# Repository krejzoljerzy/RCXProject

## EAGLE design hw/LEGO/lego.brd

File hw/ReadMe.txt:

Tutaj wrzucamy wszystkie smieci odnosnie hardware'u ;)

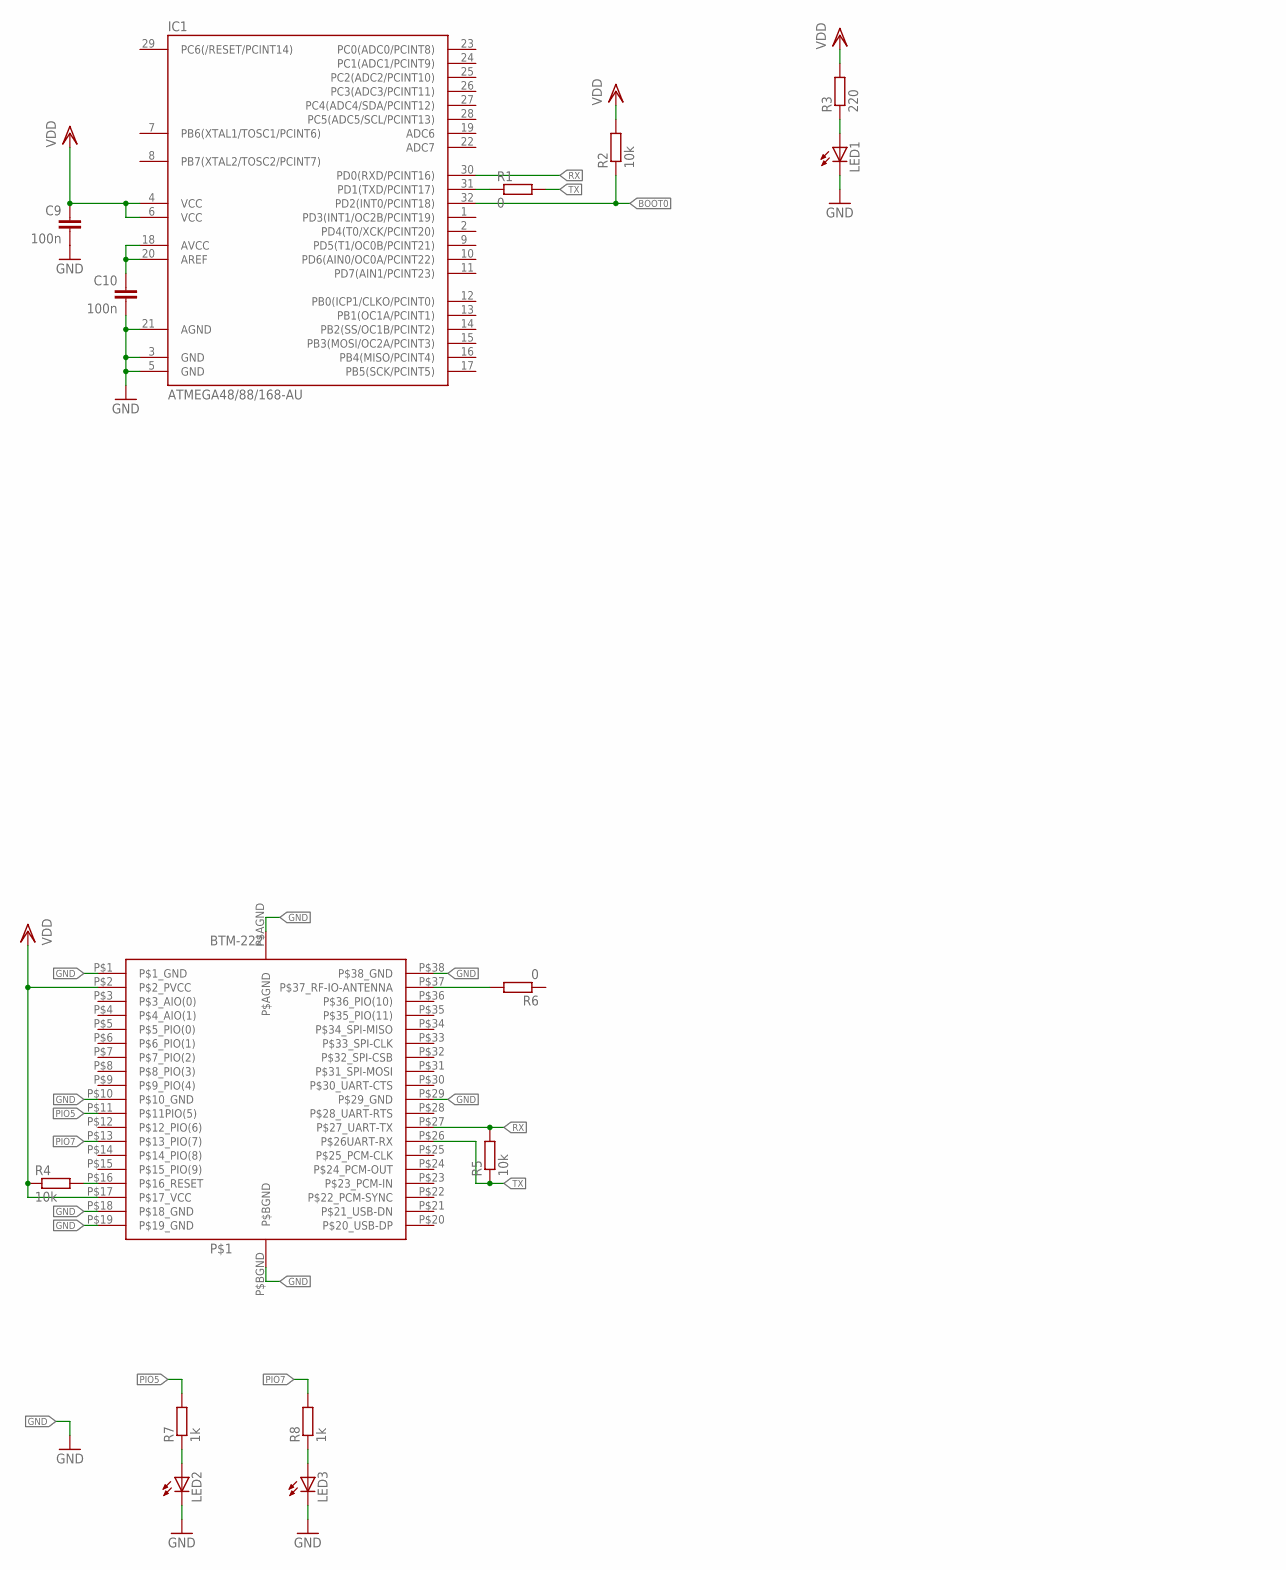
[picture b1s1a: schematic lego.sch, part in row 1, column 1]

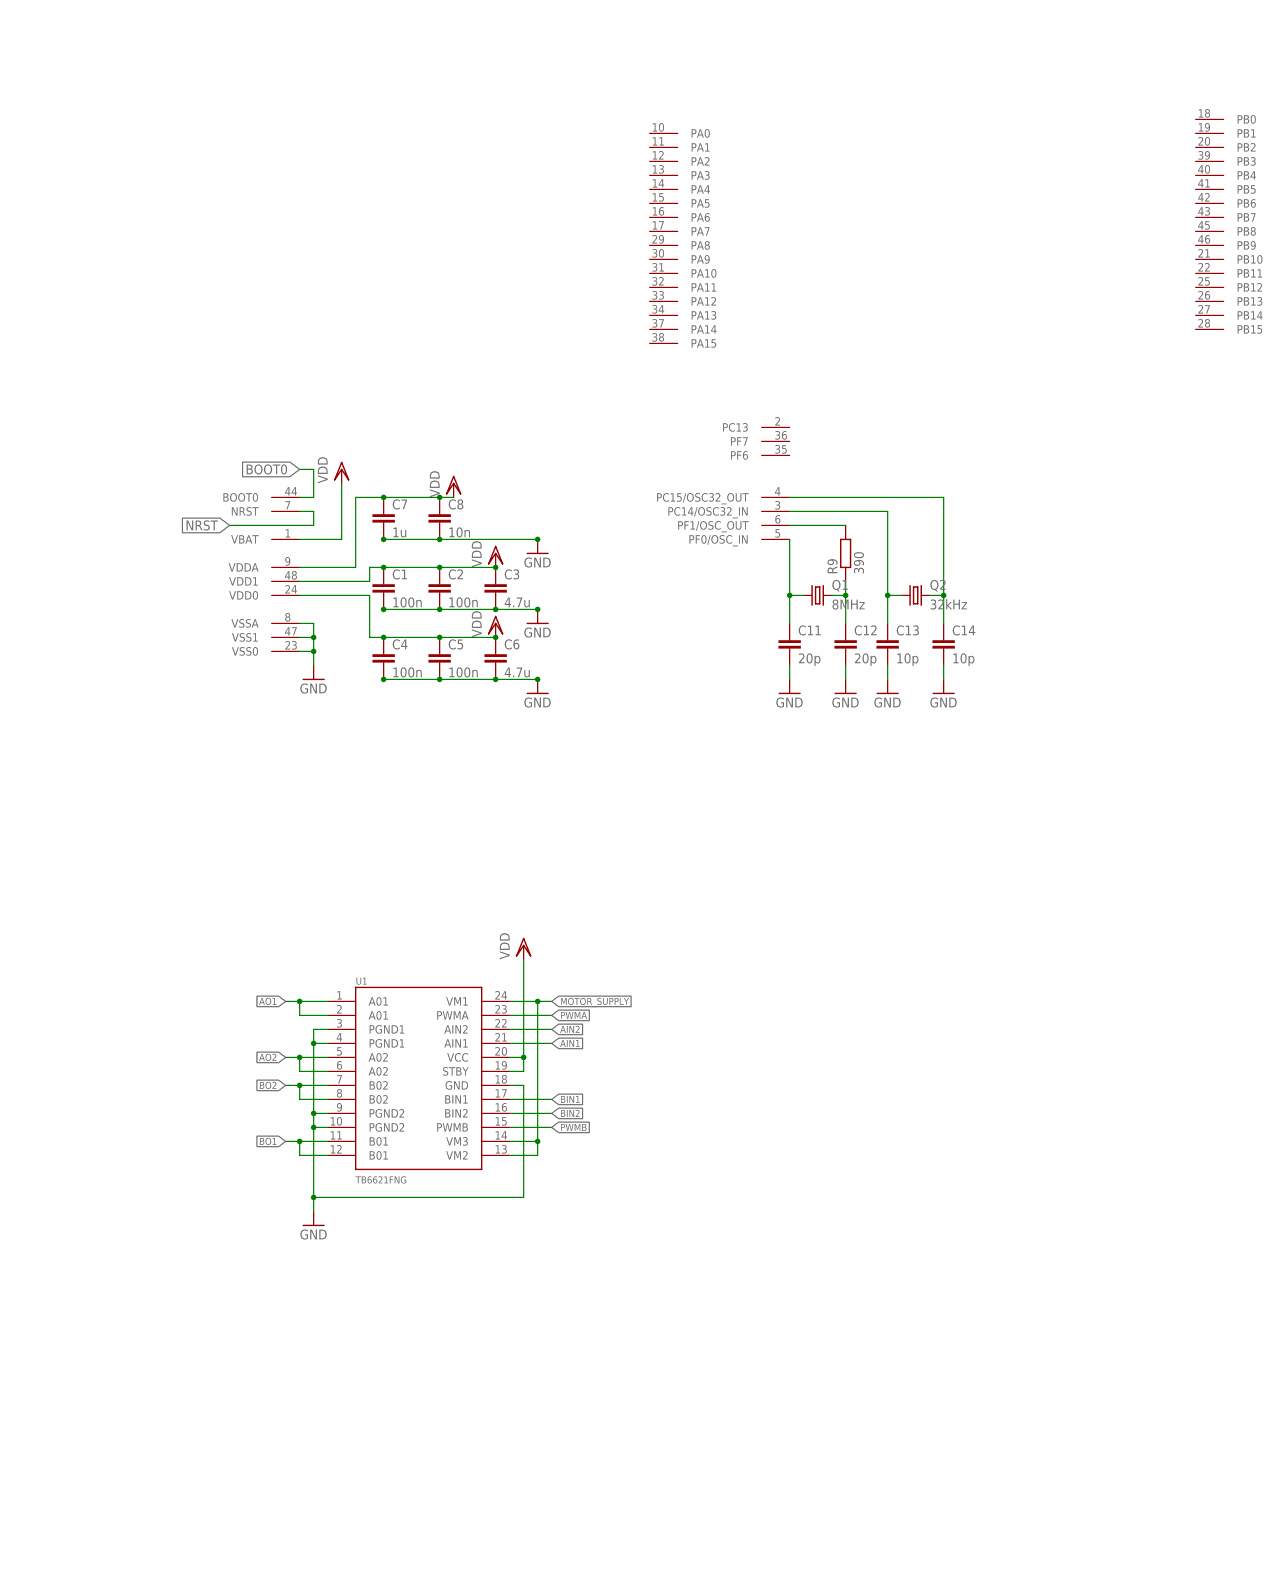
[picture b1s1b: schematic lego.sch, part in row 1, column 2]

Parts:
C1, C2, C4, C5, C9, C10: 100n; C0805
C3, C6: 4.7u; C0805
C7: 1u; C0805
C8: 10n; C0805
C11, C12: 20p; C0805
C13, C14: 10p; C0805
IC1: ATMEGA48/88/168-AU; TQFP32-08
LED1, LED2, LED3: LEDSMT1206; 1206
P$1: BTM-222
Q1: 8MHz; HC49UP
Q2: 32kHz; HC49UP
R1, R6: 0; R0805
R2, R4, R5: 10k; R0805
R3: 220; R0805
R7, R8: 1k; R0805
R9: 390; R0805
U1: TB6621FNG; SSOP24
U$1: STM32F050; LQFP48

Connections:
AIN1: U1.21 (AIN1)
AIN2: U1.22 (AIN2)
AO1: U1.1 (A01), U1.2 (A01)
AO2: U1.5 (A02), U1.6 (A02)
BIN1: U1.17 (BIN1)
BIN2: U1.16 (BIN2)
BO1: U1.11 (B01), U1.12 (B01)
BO2: U1.7 (B02), U1.8 (B02)
BOOT0: IC1.32 (PD2(INT0/PCINT18)), R2.1, U$1.44 (BOOT0)
GND: C1.2, C2.2, C3.2, C4.2, C5.2, C6.2, C7.2, C8.2, C9.2, C10.2, C11.2, C12.2, C13.2, C14.2, IC1.3 (GND), IC1.5 (GND), IC1.21 (AGND), LED1.C, LED2.C, LED3.C, P$1.P$1 (P$1_GND), P$1.P$10 (P$10_GND), P$1.P$18 (P$18_GND), P$1.P$19 (P$19_GND), P$1.P$29 (P$29_GND), P$1.P$38 (P$38_GND), P$1.P$AGND, P$1.P$BGND, U1.3 (PGND1), U1.4 (PGND1), U1.9 (PGND2), U1.10 (PGND2), U1.18 (GND), U$1.8 (VSSA), U$1.23 (VSS0), U$1.47 (VSS1)
MOTOR_SUPPLY: U1.13 (VM2), U1.14 (VM3), U1.24 (VM1)
unnamed: IC1.31 (PD1(TXD/PCINT17)), R1.1
unnamed: C10.1, IC1.18 (AVCC), IC1.20 (AREF)
unnamed: LED1.A, R3.1
unnamed: P$1.P$16 (P$16_RESET), R4.2
unnamed: P$1.P$37 (P$37_RF-IO-ANTENNA), R6.2
unnamed: LED2.A, R7.1
unnamed: LED3.A, R8.1
unnamed: R9.2, U$1.6 (PF1/OSC_OUT)
unnamed: C11.1, Q1.1, U$1.5 (PF0/OSC_IN)
unnamed: C12.1, Q1.2, R9.1
unnamed: C13.1, Q2.1, U$1.3 (PC14/OSC32_IN)
unnamed: C14.1, Q2.2, U$1.4 (PC15/OSC32_OUT)
NRST: U$1.7 (NRST)
PIO5: P$1.P$11 (P$11PIO(5)), R7.2
PIO7: P$1.P$13 (P$13_PIO(7)), R8.2
PWMA: U1.23 (PWMA)
PWMB: U1.15 (PWMB)
RX: IC1.30 (PD0(RXD/PCINT16)), P$1.P$27 (P$27_UART-TX), R5.2
TX: P$1.P$26 (P$26UART-RX), R1.2, R5.1
VDD: C1.1, C2.1, C3.1, C4.1, C5.1, C6.1, C7.1, C8.1, C9.1, IC1.4 (VCC), IC1.6 (VCC), P$1.P$2 (P$2_PVCC), P$1.P$17 (P$17_VCC), R2.2, R3.2, R4.1, U1.19 (STBY), U1.20 (VCC), U$1.1 (VBAT), U$1.9 (VDDA), U$1.24 (VDD0), U$1.48 (VDD1)

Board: 2 copper layers, 32 parts (0 on the bottom side), 24 nets, no tracks yet.

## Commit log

2013-03-17 Commit informacyjny
2013-03-17 test
2013-03-17 Revert "test"
    This reverts commit a22369d417f8c8e0417bf1dcff48e395ad6d67dc.
2013-03-17 Revert "Revert "test""
    This reverts commit 6c867d198b327fe495dcb741ff3c8d3e59af83cb.
2013-03-17 konflikt test
2013-03-17 removing unnecessary file
2013-03-17 Proper values of these files
2013-03-20 Chuj
2013-03-20 Założenia dzisiejszego spotkania
2013-03-20 merged readme file
2013-03-20 Revert "Proper values of these files"
    This reverts commit 71193483791dffe822b6f8ac4ff980ac46795a6a.
    Conflicts:
    fw/ReadMe.txt
2013-03-24 First big commit!
    CompileAndLinker:
    * Created project that compiles and links stuff for cortex-m0 form java application.
2013-03-25 CompileAndLink:
    *Added auto pathing!
2013-03-25 *Added some file ignores.
2013-03-25 *some more ignore files
2013-03-25 *some file cleaning
2013-03-25 * Added compilation batch file.
2013-03-26 RCXProject_HW:
    * Added outdated lego board design from eagle.
    * Modified gitignore.
2013-03-26 *removed garbage
2013-03-26 Removing project files. They should not be commited
2013-03-26 Hardware documentation and not very important changes
2013-03-27 Added simple html file with links to needed software.
2013-03-27 Added some ignores
2013-03-27 More ignores
2013-03-27 Removing ignored files
2013-03-27 * Added comments in java CompileAndLink project
    * Fresh batch file.
2013-04-07 added protocol definition link
2013-05-04 to jest damiana komentarz
2013-05-04 library for stm32f0**
2013-05-04 and package :)
2013-05-04 full libraries
2013-05-04 btm 222 eagle library
2013-05-04 aktualny projekt
2013-05-05 Dodany układ mostka i kwarc do stm'a
2013-05-10 Set project for Lego GUI.
    What's working:
    *adding new block (temporarily through connect button)
    *moving blocks
    *resizing blocks through mouse scroll (not final)
    *list of all blocks (program tree pending)
    *event listeners
2013-09-30 Update on GUI:
    * working single parent/child behavior.
    * working group parent/child behavior.
2013-09-30 GUI:
    * blocks child/parent behavior works, hangs in specific multiblock action
2013-11-30 SW:
    * Got the blocks zooming and moving
2013-12-28 Commiting changes
2013-12-28 GUI:
    * Fixed child/parent behavior
